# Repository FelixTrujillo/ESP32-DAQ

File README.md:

# ESP32-DAQ
This repository contains the code and design of a data acquisition device for the battery system of an electric vehicle. Developed with the ESP-WROOM-32, this device records current, voltage, speed and GPS data accurately and efficiently.

Bill of materials: ESP-WROOM-32, Current sensor ACS-712, Power module Holybro PM02, Hall effect sensor KY-024, NEO-6M GPS module, Micro SD storage module, T-D500 Temperature Sensor

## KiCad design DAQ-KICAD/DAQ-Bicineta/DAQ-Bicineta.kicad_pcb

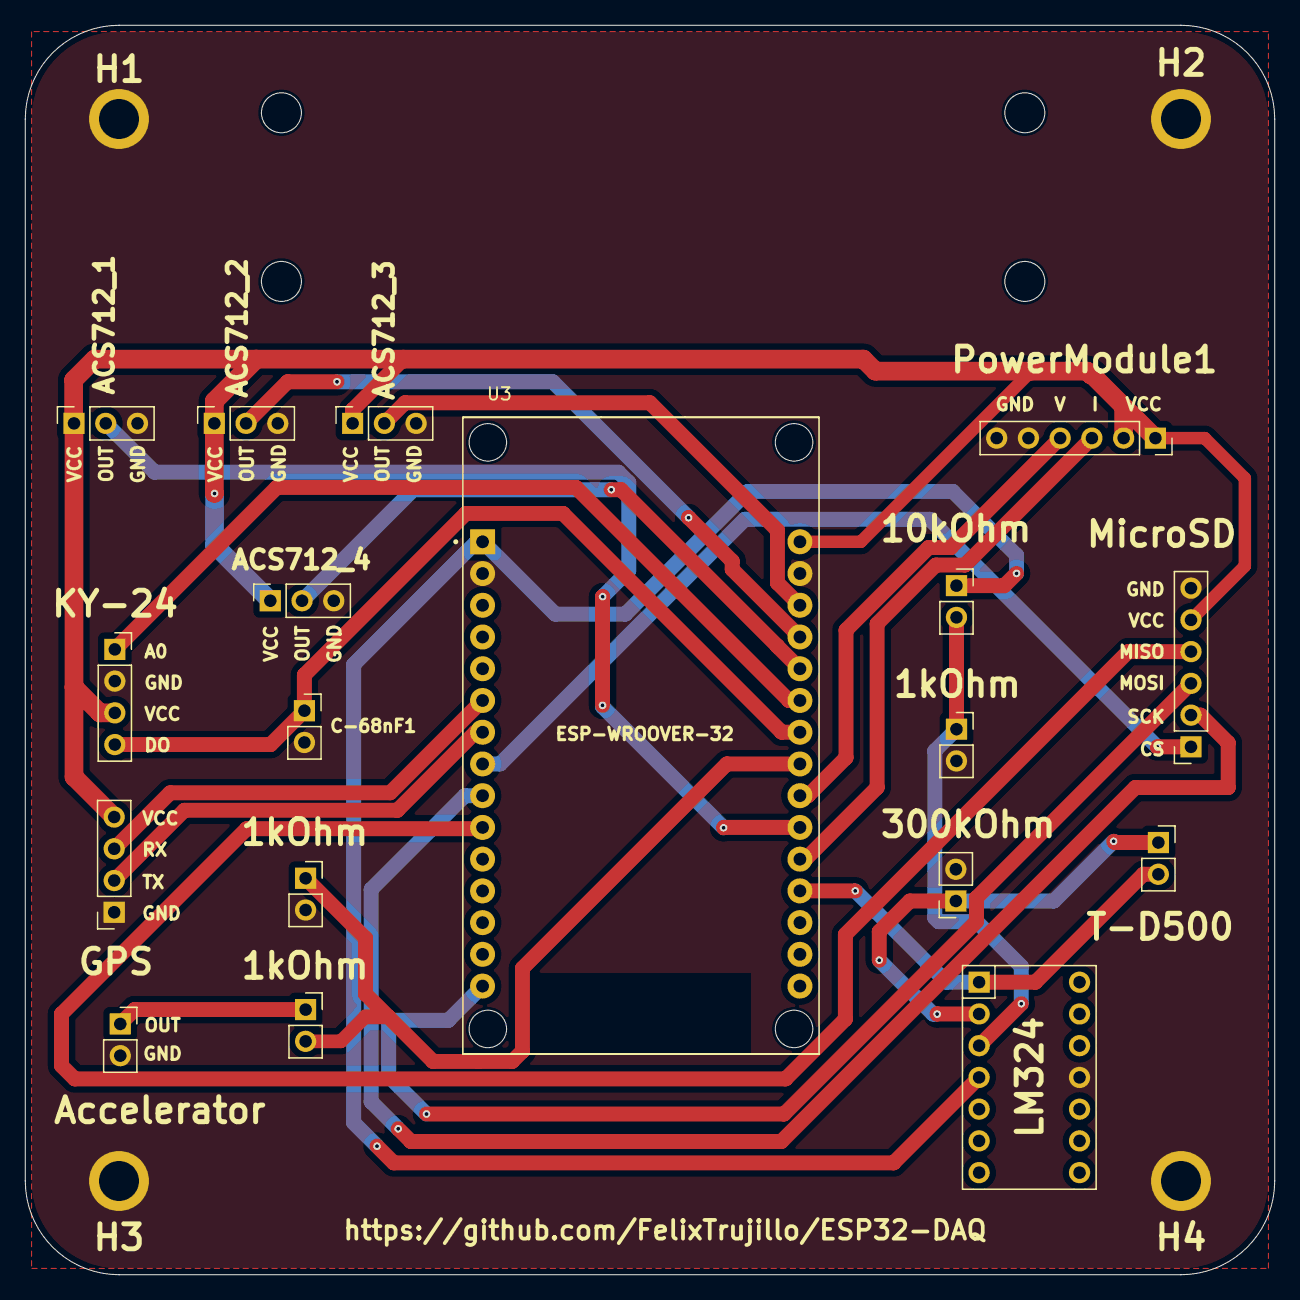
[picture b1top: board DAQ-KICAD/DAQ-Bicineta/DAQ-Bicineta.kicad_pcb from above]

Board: 2 copper layers, 100.0 x 100.0 mm, 22 parts (0 on the bottom side), 22 nets.

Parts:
1kOhm, 1kOhm#2, 1kOhm#3, 10kOhm, 300kOhm: R; PinSocket_1x02_P2.54mm_Vertical
ACS712_1, ACS712_2, ACS712_3, ACS712_4: Conn_01x03; PinSocket_1x03_P2.54mm_Vertical
Accelerator: Conn_01x02; PinSocket_1x02_P2.54mm_Vertical
C-68nF1: C_Small; PinSocket_1x02_P2.54mm_Vertical
GPS: Conn_01x04; PinSocket_1x04_P2.54mm_Vertical
H1, H2, H3, H4: MountingHole_2.2mm_M2_ISO7380_Pad
KY-24: Conn_01x04; PinSocket_1x04_P2.54mm_Vertical
LM324: Conn_02x07_Odd_Even; LM324
MicroSD: Conn_01x06; PinSocket_1x06_P2.54mm_Vertical
PowerModule1: Conn_01x06; PinSocket_1x06_P2.54mm_Vertical
T-D500: Conn_01x02; PinSocket_1x02_P2.54mm_Vertical
U3: ESP32-DEVKIT-V1; MODULE_ESP32_DEVKIT_V1

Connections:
ACCELERATOR_GND: 1kOhm#2.2, 1kOhm#3.2, 300kOhm.2, ACS712_1.3, ACS712_2.3, ACS712_3.3, ACS712_4.3, Accelerator.2, C-68nF1.2, GPS.1, H1.1, H2.2, H3.3, H4.4, KY-24.2, LM324.8, MicroSD.6, PowerModule1.5, PowerModule1.6, U3.2 (GND), U3.29 (GND)
ACCELERATOR_Vout: 1kOhm.2, 1kOhm#3.1, U3.23 (D25)
CS_OUT_1: ACS712_1.2, U3.21 (D32)
CS_OUT_2: ACS712_2.2, U3.27 (D12)
CS_OUT_3: ACS712_3.2, U3.28 (D13)
CS_OUT_4: ACS712_4.2, U3.26 (D14)
CS_VCC: ACS712_1.1, ACS712_2.1, ACS712_3.1, ACS712_4.1, GPS.4, KY-24.3, MicroSD.5, PowerModule1.1, PowerModule1.2, U3.30 (VIN)
GPS_RX: GPS.3, U3.6 (RX2)
GPS_TX: GPS.2, U3.7 (TX2)
KY_A0: KY-24.1, U3.25 (D27)
KY_DO: C-68nF1.1, KY-24.4, U3.24 (D26)
MSD_CS: MicroSD.1, U3.8 (D5)
MSD_MISO: MicroSD.4, U3.10 (D19)
MSD_MOSI: MicroSD.3, U3.15 (D23)
MSD_SCK: MicroSD.2, U3.9 (D18)
unnamed: 1kOhm.1, Accelerator.1
unnamed: 300kOhm.1, LM324.3, T-D500.1
unnamed: 1kOhm#2.1, 10kOhm.2, LM324.5
PM_I: PowerModule1.3, U3.20 (D35)
PM_V: PowerModule1.4, U3.22 (D33)
T-D500_OUT: LM324.1, T-D500.2, U3.19 (D34)
T-D500_VCC: 10kOhm.1, LM324.7, U3.1 (3V3)

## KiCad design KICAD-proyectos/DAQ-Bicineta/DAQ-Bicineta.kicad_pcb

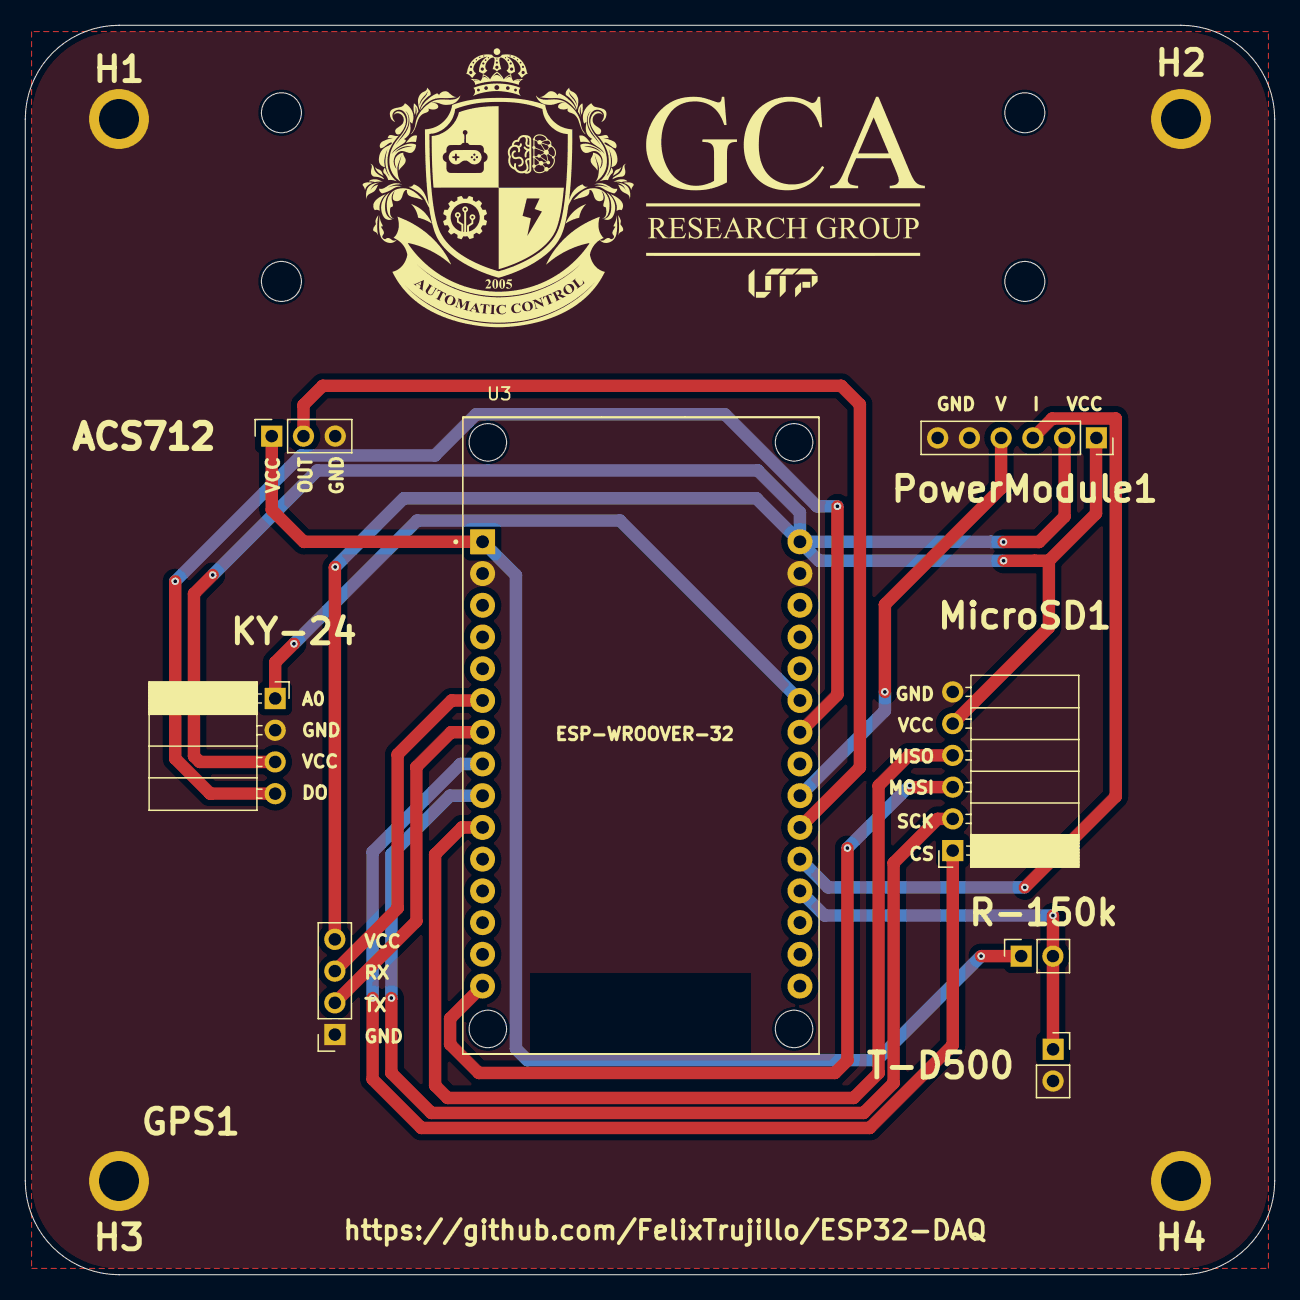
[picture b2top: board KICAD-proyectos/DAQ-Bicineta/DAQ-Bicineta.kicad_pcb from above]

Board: 2 copper layers, 100.0 x 100.0 mm, 12 parts (0 on the bottom side), 15 nets.

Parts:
ACS712: Conn_01x03; PinSocket_1x03_P2.54mm_Vertical
GPS1: Conn_01x04; PinSocket_1x04_P2.54mm_Vertical
H1, H2, H3, H4: MountingHole_2.2mm_M2_ISO7380_Pad
KY-24: Conn_01x04; PinSocket_1x04_P2.54mm_Horizontal
MicroSD1: Conn_01x06; PinSocket_1x06_P2.54mm_Horizontal
PowerModule1: Conn_01x06; PinSocket_1x06_P2.54mm_Vertical
R-150k: R; PinSocket_1x02_P2.54mm_Vertical
T-D500: Conn_01x02; PinSocket_1x02_P2.54mm_Vertical
U3: ESP32-DEVKIT-V1; MODULE_ESP32_DEVKIT_V1

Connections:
CS_GND: ACS712.3, GPS1.1, H1.1, H2.2, H3.3, H4.4, KY-24.2, MicroSD1.6, PowerModule1.5, PowerModule1.6, T-D500.2, U3.2 (GND), U3.29 (GND)
CS_OUT: ACS712.2, U3.21 (D32)
CS_VCC: ACS712.1, R-150k.1, U3.1 (3V3)
GPS_RX: GPS1.3, U3.6 (RX2)
GPS_TX: GPS1.2, U3.7 (TX2)
GPS_VCC: GPS1.4, KY-24.3, MicroSD1.5, PowerModule1.1, PowerModule1.2, U3.30 (VIN)
KY_A0: KY-24.1, U3.25 (D27)
KY_DO: KY-24.4, U3.24 (D26)
MSD_CS: MicroSD1.1, U3.8 (D5)
MSD_MISO: MicroSD1.4, U3.10 (D19)
MSD_MOSI: MicroSD1.3, U3.15 (D23)
MSD_SCK: MicroSD1.2, U3.9 (D18)
PM_I: PowerModule1.3, U3.20 (D35)
PM_V: PowerModule1.4, U3.22 (D33)
T-D500_OUT: R-150k.2, T-D500.1, U3.19 (D34)

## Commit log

2024-04-16 Upload Project Files
    In this commit the addition of the different parts of the project is carried out, both the addition of the code and the PCB design.
2024-04-22 DAQ_STEP
    The PCB modifications are made to incorporate the T-D500 and the CAD design of the DAQ card is carried out.
2024-04-22 Name update
    The modification of the folder names is carried out
2024-06-06 PCB-Validation
    The necessary tests and modifications for the final operation on the printed circuit board are carried out; the validation of the GPS functionality is still pending.
2024-06-21 Sensor-Calibration
    Calibration of the current, temperature sensors
2024-06-24 Update of Temperature Sensor and Hall Effect Parameters
    The temperature sensor was calibrated to update the parameters of the equation, and the Hall effect sensor was optimally coupled.
2024-06-24 Introduction to the Uplox 6m GPS Sensor
    The Ublo-6m sensor is configured and implemented on the data acquisition board. Additionally, the code is reviewed to clean and organize it, removing the current1 value from the power module's curren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
2024-07-09 Images
    Uploading images for the documentation of the respository.
2024-07-19 T-D500 and KY-024 calibration
2024-07-22 Create .gitignore - Unity
2024-07-22 .gitignore update
2024-07-22 DAQ-APP_update
2024-07-29 DAQ-V2-KICAD-modification
2024-07-30 Bicineta_Path_Data_update
2024-08-17 IdentificationCode
2024-08-17 DAQ-Interface_Modifications
    Modification and development of the interaction between systems across scenes.
2024-08-20 Graph Integration - DAQInterface
2024-08-20 Graph-Update-Modification
2024-08-20 Update-GraphParameters
2024-08-31 UI/UX-DAQ-Demo
2024-09-17 Update-DAQ
2024-09-24 Preliminar Version DAQ
2024-09-24 Matlab Identification - Folder
2025-06-11 Update LICENSE
